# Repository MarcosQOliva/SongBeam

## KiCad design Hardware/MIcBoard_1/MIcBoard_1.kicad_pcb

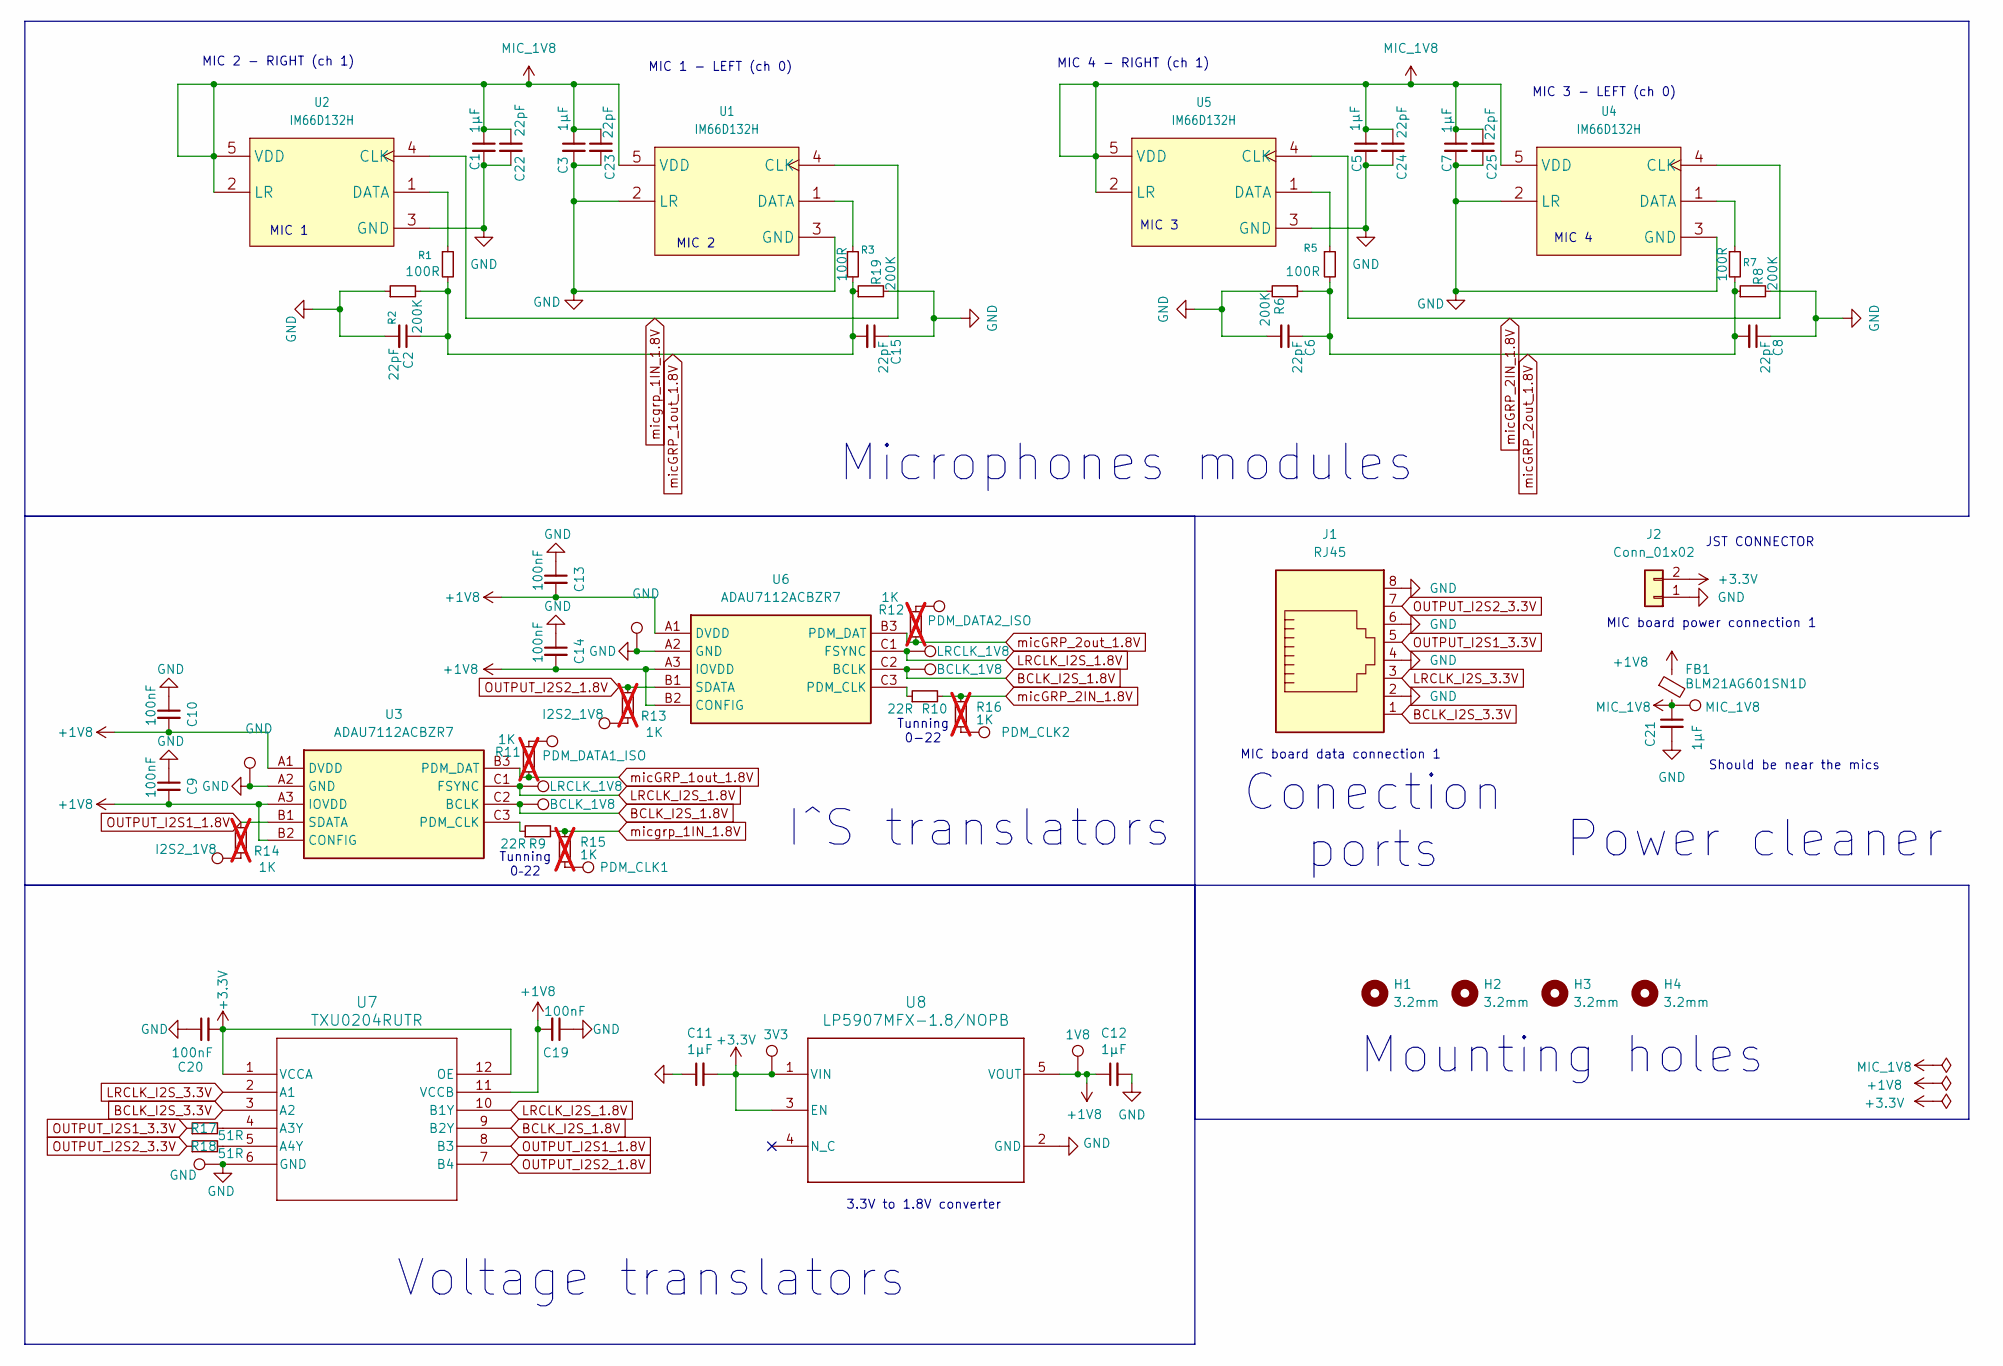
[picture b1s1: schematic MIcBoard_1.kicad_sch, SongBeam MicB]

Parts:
1V8, 3V3: TestPoint; TestPoint_Pad_D1.0mm
C1, C3, C5, C7, C11, C12, C21: 1µF; C_0805_2012Metric; Voltage 25V
C2, C6, C8, C15, C22, C23, C24, C25: 22pF; C_0805_2012Metric; Voltage 50V
C9, C10, C13, C14, C19, C20: 100nF; C_0805_2012Metric; Voltage 25V
FB1: BLM21AG601SN1D; L_0805_2012Metric
H1, H2, H3, H4: 3.2mm; MountingHole_3.2mm_M3_ISO14580
J1: RJ45; RJHSE5380_AMP
J2: Conn_01x02; CONN_S2B-XH-A_JST
R1, R3, R5, R7: 100R; R_0805_2012Metric
R2, R6, R8, R19: 200K; R_0805_2012Metric
R9, R10: 22R; R_0805_2012Metric
R11, R12, R13, R14, R15, R16: 1K; R_0805_2012Metric; not fitted
R17, R18: 51R; R_0805_2012Metric
TP3: PDM_DATA1_ISO; TestPoint_Pad_D1.0mm
TP4: PDM_DATA2_ISO; TestPoint_Pad_D1.0mm
TP5: MIC_1V8; TestPoint_Pad_D1.0mm
TP6, TP7, TP15: GND; TestPoint_Pad_D1.0mm
TP12, TP19: BCLK_1V8; TestPoint_Pad_D1.0mm
TP13, TP18: LRCLK_1V8; TestPoint_Pad_D1.0mm
TP16: PDM_CLK1; TestPoint_Pad_D1.0mm
TP17, TP21: I2S2_1V8; TestPoint_Pad_D1.0mm
TP20: PDM_CLK2; TestPoint_Pad_D1.0mm
U1, U2, U4, U5: IM66D132H; IFX-PG-TLGA-5N-9-V
U3, U6: ADAU7112ACBZR7; BGA9C40P3X3_126X126X56; Manufacturer_Part_Number ADAU7112ACBZR7; Mouser Part Number 584-AU7112ACBZR7
U7: TXU0204RUTR; QFN_04RUTR_TEX
U8: LP5907MFX-1.8/NOPB; DBV0005A_N

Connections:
+1V8: 1V8.1 (1_1), C9.2, C10.2, C12.1, C13.2, C14.2, C19.2, FB1.1, U3.A1 (DVDD), U3.A3 (IOVDD), U3.B2 (CONFIG), U6.A1 (DVDD), U6.A3 (IOVDD), U6.B2 (CONFIG), U7.11 (VCCB), U8.5 (VOUT)
+3.3V: 3V3.1 (1_1), C11.2, C20.2, J2.2, U7.1 (VCCA), U7.12 (OE), U8.1 (VIN), U8.3 (EN)
BCLK_I2S_1.8V: TP12.1 (1_1), TP19.1 (1_1), U3.C2 (BCLK), U6.C2 (BCLK), U7.9 (B2Y)
BCLK_I2S_3.3V: J1.1, U7.3 (A2)
GND: C1.2, C2.2, C3.2, C5.2, C6.2, C7.2, C8.1, C9.1, C10.1, C11.1, C12.2, C13.1, C14.1, C15.1, C19.1, C20.1, C21.2, C22.2, C23.2, C24.2, C25.2, J1.2, J1.4, J1.6, J1.8, J2.1, R2.1, R6.2, R8.2, R19.2, TP6.1 (1_1), TP7.1 (1_1), TP15.1 (1_1), U1.2 (LR), U1.3 (GND), U2.3 (GND), U3.A2 (GND), U4.2 (LR), U4.3 (GND), U5.3 (GND), U6.A2 (GND), U7.6 (GND), U8.2 (GND)
LRCLK_I2S_1.8V: TP13.1 (1_1), TP18.1 (1_1), U3.C1 (FSYNC), U6.C1 (FSYNC), U7.10 (B1Y)
LRCLK_I2S_3.3V: J1.3, U7.2 (A1)
MIC_1V8: C1.1, C3.1, C5.1, C7.1, C21.1, C22.1, C23.1, C24.1, C25.1, FB1.2, TP5.1 (1_1), U1.5 (VDD), U2.2 (LR), U2.5 (VDD), U4.5 (VDD), U5.2 (LR), U5.5 (VDD)
unnamed: R11.2, TP3.1 (1_1)
unnamed: R12.2, TP4.1 (1_1)
unnamed: R13.1, TP17.1 (1_1)
unnamed: R14.1, TP21.1 (1_1)
unnamed: R15.2, TP16.1 (1_1)
unnamed: R16.2, TP20.1 (1_1)
unnamed: R3.1, U1.1 (DATA)
unnamed: R1.1, U2.1 (DATA)
unnamed: R9.1, U3.C3 (PDM_CLK)
unnamed: R7.1, U4.1 (DATA)
unnamed: R5.1, U5.1 (DATA)
unnamed: R10.1, U6.C3 (PDM_CLK)
unnamed: R17.2, U7.4 (A3Y)
unnamed: R18.2, U7.5 (A4Y)
OUTPUT_I2S1_1.8V: R14.2, U3.B1 (SDATA), U7.8 (B3)
OUTPUT_I2S1_3.3V: J1.5, R17.1
OUTPUT_I2S2_1.8V: R13.2, U6.B1 (SDATA), U7.7 (B4)
OUTPUT_I2S2_3.3V: J1.7, R18.1
micGRP_1out_1.8V: C2.1, C15.2, R1.2, R2.2, R3.2, R11.1, R19.1, U3.B3 (PDM_DAT)
micGRP_2IN_1.8V: R10.2, R16.1, U4.4 (CLK), U5.4 (CLK)
micGRP_2out_1.8V: C6.1, C8.2, R5.2, R6.1, R7.2, R8.1, R12.1, U6.B3 (PDM_DAT)
micgrp_1IN_1.8V: R9.2, R15.1, U1.4 (CLK), U2.4 (CLK)

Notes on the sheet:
Microphones modules
MIC 1 - LEFT (ch 0)
Should be near the mics
Voltage translators
Power cleaner
JST CONNECTOR
MIC 4 - RIGHT (ch 1)
MIC 1
MIC 2
Tunning 0-22
Tunning 0–22
MIC 3
3.3V to 1.8V converter
MIC 4
Conection ports
Mounting holes
MIC 2 - RIGHT (ch 1)
MIC board data connection 1
I^S translators
MIC board power connection 1
MIC 3 - LEFT (ch 0)

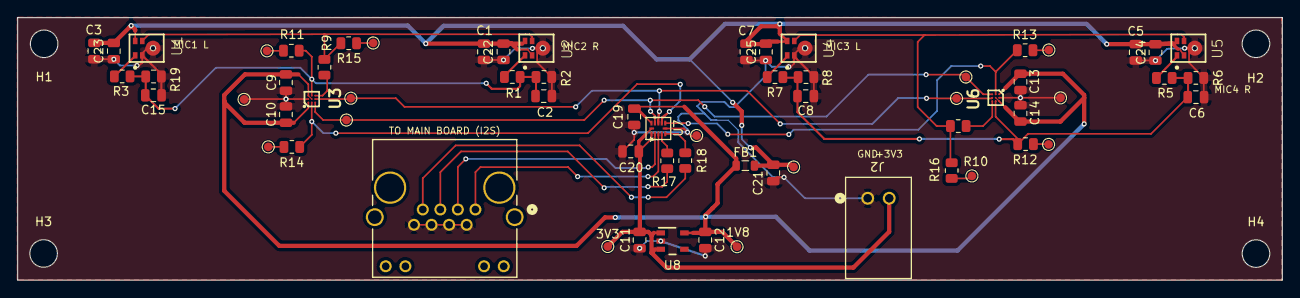
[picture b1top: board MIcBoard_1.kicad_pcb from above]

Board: 2 copper layers, 147.0 x 30.5 mm, 70 parts (0 on the bottom side), 30 nets.

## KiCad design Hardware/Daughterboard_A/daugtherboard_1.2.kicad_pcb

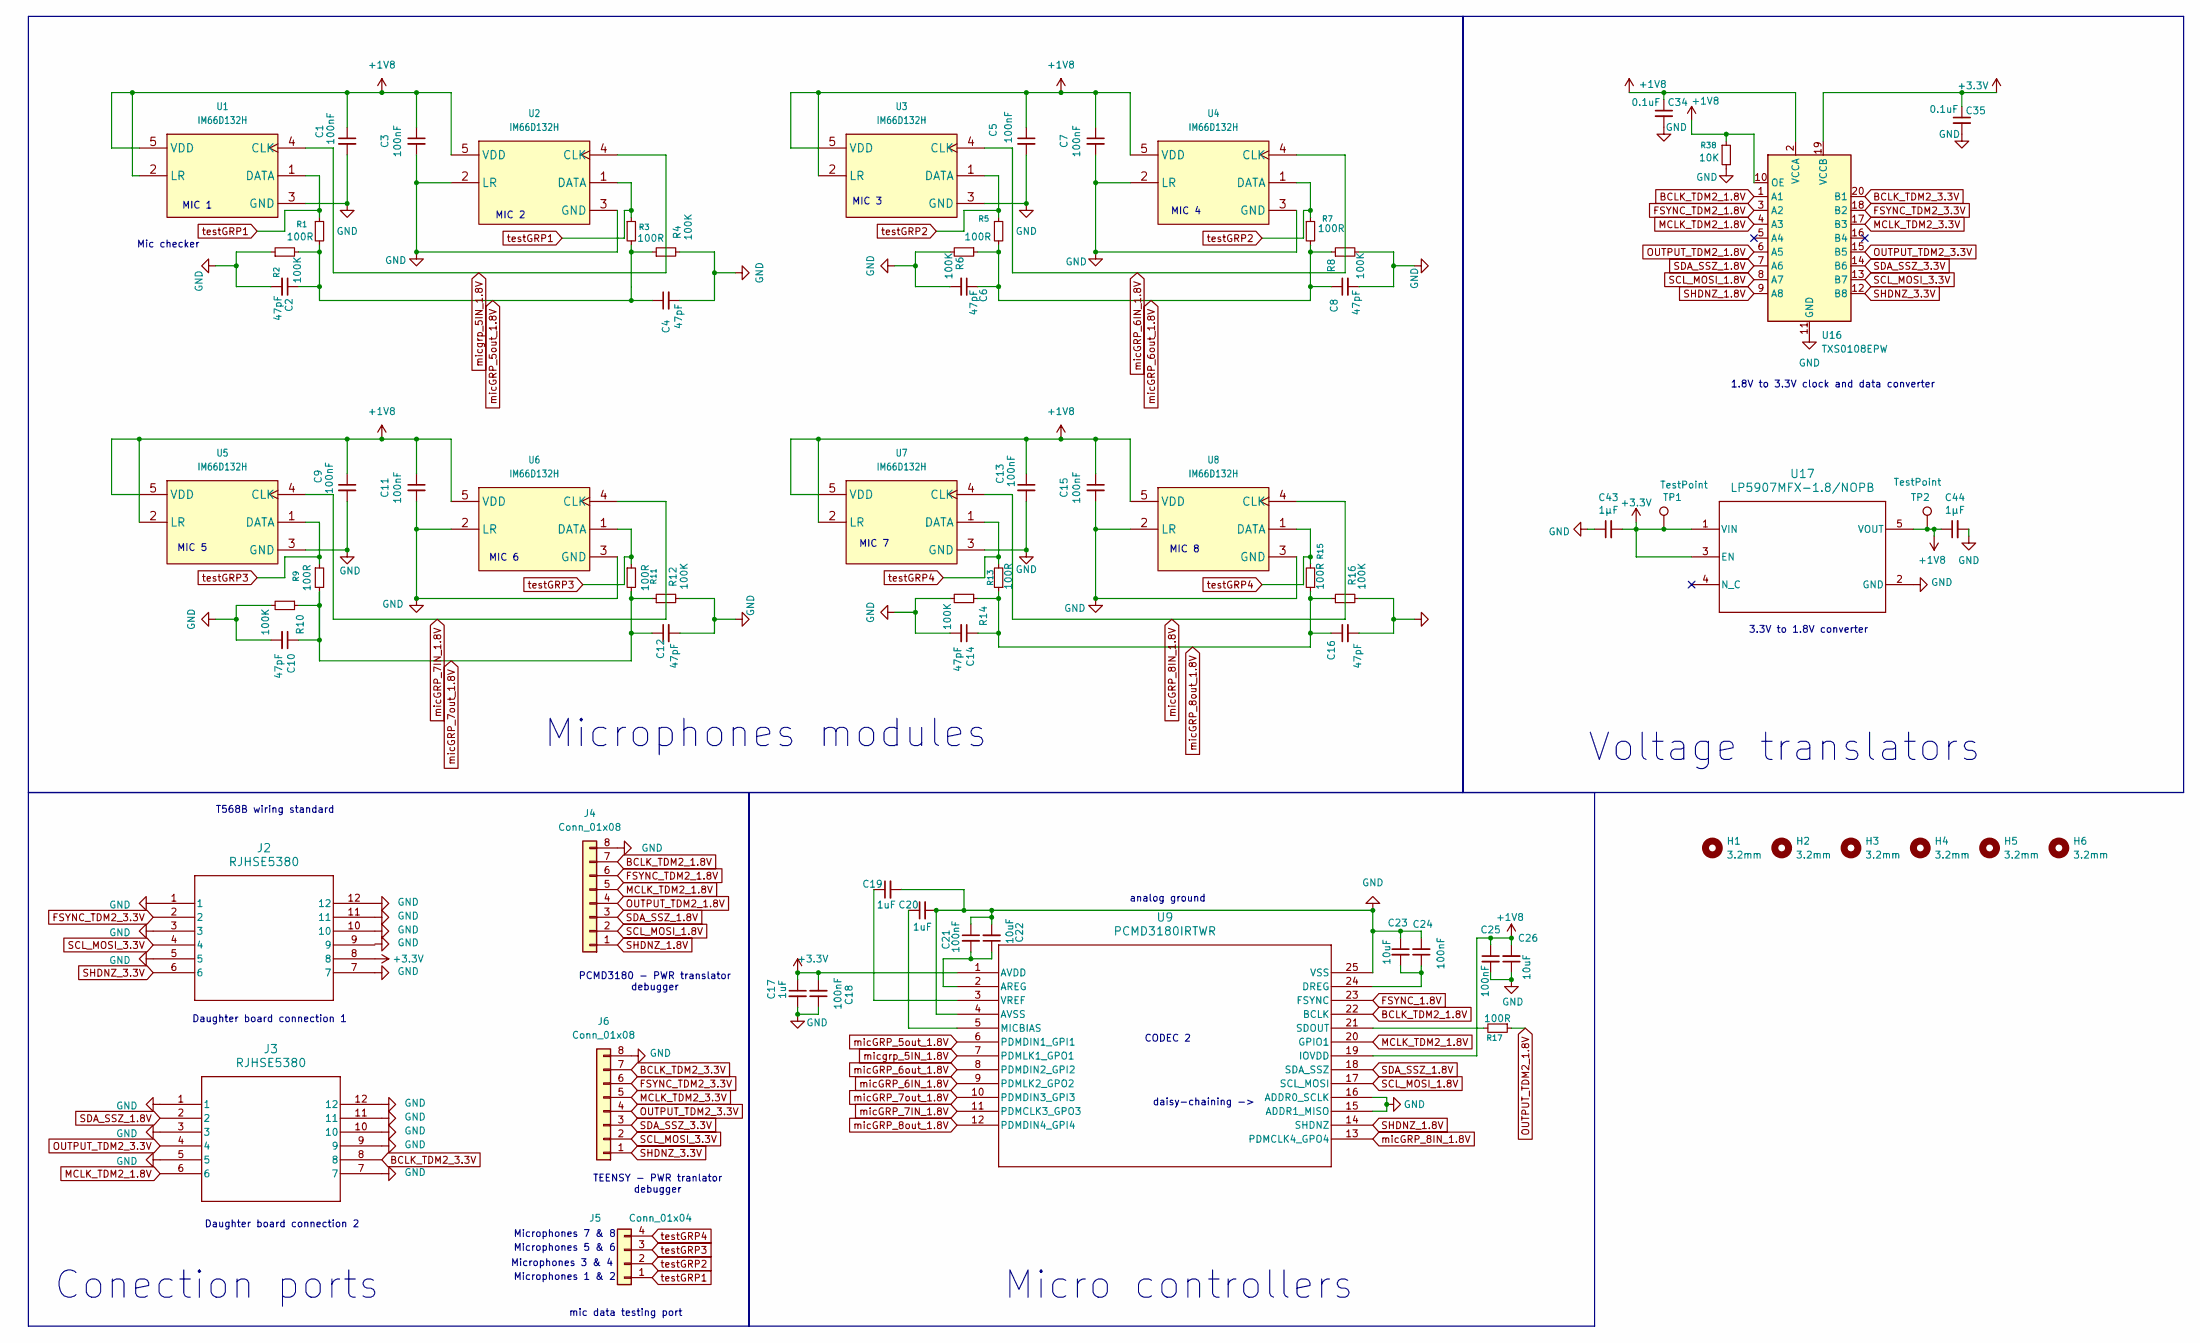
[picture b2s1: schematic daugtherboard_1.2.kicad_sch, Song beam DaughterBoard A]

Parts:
C1, C3, C5, C7, C9, C11, C13, C15, C18, C21, C24, C25: 100nF; C_0805_2012Metric
C2, C4, C6, C8, C10, C12, C14, C16: 47pF; C_0805_2012Metric
C17, C19, C20: 1uF; C_0805_2012Metric
C22, C23, C26: 10uF; C_0805_2012Metric
C34, C35: 0.1uF; C_0805_2012Metric
C43, C44: 1µF; C_0805_2012Metric
H1, H2, H3, H4, H5, H6: 3.2mm; MountingHole_3.2mm_M3_ISO14580
J2, J3: RJHSE5380; RJHSE5380_AMP
J4, J6: Conn_01x08; PinHeader_1x08_P2.00mm_Vertical
J5: Conn_01x04; PinHeader_1x04_P2.00mm_Vertical
R1, R3, R5, R7, R9, R11, R13, R15, R17: 100R; R_0805_2012Metric
R2, R4, R6, R8, R10, R12, R14, R16: 100K; R_0805_2012Metric
R38: 10K; R_0805_2012Metric
TP1, TP2: TestPoint; TestPoint_Pad_D1.0mm
U1, U2, U3, U4, U5, U6, U7, U8: IM66D132H; IFX-PG-TLGA-5N-9-V
U9: PCMD3180IRTWR
U16: TXS0108EPW; TSSOP-20_4.4x6.5mm_P0.65mm
U17: LP5907MFX-1.8/NOPB; DBV0005A_N

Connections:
+1V8: C1.1, C3.1, C5.1, C7.1, C9.1, C11.1, C13.1, C15.1, C25.1, C26.2, C34.1, C44.1, R38.1, TP2.1, U1.2 (LR), U1.5 (VDD), U2.5 (VDD), U3.2 (LR), U3.5 (VDD), U4.5 (VDD), U5.2 (LR), U5.5 (VDD), U6.5 (VDD), U7.2 (LR), U7.5 (VDD), U8.5 (VDD), U9.19 (IOVDD), U16.2 (VCCA), U16.10 (OE), U17.5 (VOUT)
+3.3V: C17.1, C18.2, C35.1, C43.2, J2.8, TP1.1, U9.1 (AVDD), U16.19 (VCCB), U17.1 (VIN), U17.3 (EN)
BCLK_TDM2_1.8V: J4.7, U9.22 (BCLK), U16.1 (A1)
BCLK_TDM2_3.3V: J3.8, J6.7, U16.20 (B1)
FSYNC_1.8V: U9.23 (FSYNC)
FSYNC_TDM2_1.8V: J4.6, U16.3 (A2)
FSYNC_TDM2_3.3V: J2.2, J6.6, U16.18 (B2)
GND: C1.2, C2.2, C3.2, C4.2, C5.2, C6.2, C7.2, C8.2, C9.2, C10.2, C11.2, C12.2, C13.2, C14.2, C15.2, C16.2, C17.2, C18.1, C19.2, C20.2, C21.1, C22.2, C23.1, C24.2, C25.2, C26.1, C34.2, C35.2, C43.1, C44.2, J2.1, J2.3, J2.5, J2.7, J2.10, J2.11, J2.12, J3.1, J3.3, J3.5, J3.7, J3.9, J3.10, J3.11, J3.12, J4.8, J6.8, R2.1, R4.2, R6.2, R8.2, R10.2, R12.2, R14.2, R16.2, R38.2, U1.3 (GND), U2.2 (LR), U2.3 (GND), U3.3 (GND), U4.2 (LR), U4.3 (GND), U5.3 (GND), U6.2 (LR), U6.3 (GND), U7.3 (GND), U8.2 (LR), U8.3 (GND), U9.4 (AVSS), U9.15 (ADDR1_MISO), U9.16 (ADDR0_SCLK), U9.25 (VSS), U16.11 (GND), U17.2 (GND)
MCLK_TDM2_1.8V: J3.6, J4.5, U9.20 (GPIO1), U16.4 (A3)
MCLK_TDM2_3.3V: J6.5, U16.17 (B3)
unnamed: C21.2, C22.1, U9.2 (AREG)
unnamed: C23.2, C24.1, U9.24 (DREG)
unnamed: C20.1, U9.5 (MICBIAS)
unnamed: R17.2, U9.21 (SDOUT)
unnamed: C19.1, U9.3 (VREF)
OUTPUT_TDM2_1.8V: J4.4, R17.1, U16.6 (A5)
OUTPUT_TDM2_3.3V: J3.4, J6.4, U16.15 (B5)
SCL_MOSI_1.8V: J4.2, U9.17 (SCL_MOSI), U16.8 (A7)
SCL_MOSI_3.3V: J2.4, J6.2, U16.13 (B7)
SDA_SSZ_1.8V: J3.2, J4.3, U9.18 (SDA_SSZ), U16.7 (A6)
SDA_SSZ_3.3V: J6.3, U16.14 (B6)
SHDNZ_1.8V: J4.1, U9.14 (SHDNZ), U16.9 (A8)
SHDNZ_3.3V: J2.6, J6.1, U16.12 (B8)
micGRP_5out_1.8V: C2.1, C4.1, R1.2, R2.2, R3.2, R4.1, U9.6 (PDMDIN1_GPI1)
micGRP_6IN_1.8V: U3.4 (CLK), U4.4 (CLK), U9.9 (PDMLK2_GPO2)
micGRP_6out_1.8V: C6.1, C8.1, R5.2, R6.1, R7.2, R8.1, U9.8 (PDMDIN2_GPI2)
micGRP_7IN_1.8V: U5.4 (CLK), U6.4 (CLK), U9.11 (PDMCLK3_GPO3)
micGRP_7out_1.8V: C10.1, C12.1, R9.2, R10.1, R11.2, R12.1, U9.10 (PDMDIN3_GPI3)
micGRP_8IN_1.8V: U7.4 (CLK), U8.4 (CLK), U9.13 (PDMCLK4_GPO4)
micGRP_8out_1.8V: C14.1, C16.1, R13.1, R14.1, R15.1, R16.1, U9.12 (PDMDIN4_GPI4)
micgrp_5IN_1.8V: U1.4 (CLK), U2.4 (CLK), U9.7 (PDMLK1_GPO1)
testGRP1: J5.1, R1.1, R3.1, U1.1 (DATA), U2.1 (DATA)
testGRP2: J5.2, R5.1, R7.1, U3.1 (DATA), U4.1 (DATA)
testGRP3: J5.3, R9.1, R11.1, U5.1 (DATA), U6.1 (DATA)
testGRP4: J5.4, R13.2, R15.2, U7.1 (DATA), U8.1 (DATA)

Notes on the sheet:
Mic checker
MIC 7
TEENSY - PWR tranlator debugger
MIC 1
3.3V to 1.8V converter
Microphones 3 & 4
analog ground
MIC 5
Voltage translators
MIC 8
Daughter board connection 1
CODEC 2
PCMD3180 - PWR translator debugger
Microphones modules
MIC 6
Microphones 7 & 8
1.8V to 3.3V clock and data converter
Daughter board connection 2
Micro controllers
Microphones 1 & 2
daisy-chaining ->
T568B wiring standard
Microphones 5 & 6
MIC 2
MIC 4
Conection ports
MIC 3
mic data testing port

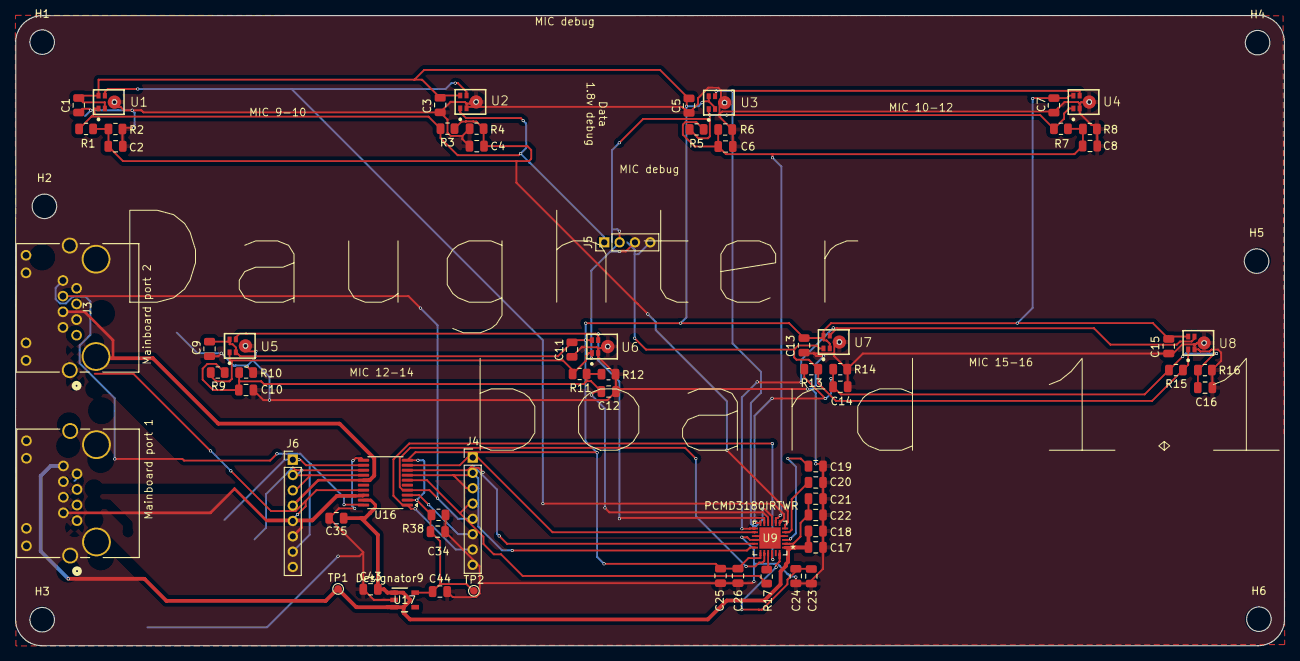
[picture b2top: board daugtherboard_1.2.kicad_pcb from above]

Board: 2 copper layers, 165.6 x 82.3 mm, 72 parts (0 on the bottom side), 34 nets.

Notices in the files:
Hardware/Daughterboard_A/daugtherboard_1.2.kicad_sch:
Creative Commons Attribution 4.0 International License
Hardware/SongBeam 3.1_kicad/SongBeam3.1.kicad_pcb:
CC BY 4.0
parts and their libraries:
Copyright 2016 Accelerated Designs. All rights reserved.
